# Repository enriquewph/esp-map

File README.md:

<!-- PROJECT SHIELDS -->
<div align="center">

[![Contributors][contributors-shield]][contributors-url]
[![Forks][forks-shield]][forks-url]
[![Stargazers][stars-shield]][stars-url]
[![Issues][issues-shield]][issues-url]
[![MIT License][license-shield]][license-url]

</div>

<p align="center">
  <picture>
    <source media="(prefers-color-scheme: dark)" srcset="docs/logo/espmap_nobg.svg">
    
  </picture>
</p>
<h1 align="center"><b>ESP</b> - <b>M</b>odular <b>A</b>utomation <b>P</b>latform</h1>
<h3 align="center">Modular hardware for IoT & home automation</h3>

<p align="center">
  <a href="https://github.com/enriquewph/esp-map"><strong>Explore the docs »</strong></a>
</p>

<!-- MARKDOWN LINKS & IMAGES -->
[contributors-shield]: https://img.shields.io/github/contributors/enriquewph/esp-map.svg?style=for-the-badge
[contributors-url]: https://github.com/enriquewph/esp-map/graphs/contributors
[forks-shield]: https://img.shields.io/github/forks/enriquewph/esp-map.svg?style=for-the-badge
[forks-url]: https://github.com/enriquewph/esp-map/network/members
[stars-shield]: https://img.shields.io/github/stars/enriquewph/esp-map.svg?style=for-the-badge
[stars-url]: https://github.com/enriquewph/esp-map/stargazers
[issues-shield]: https://img.shields.io/github/issues/enriquewph/esp-map.svg?style=for-the-badge
[issues-url]: https://github.com/enriquewph/esp-map/issues
[license-shield]: https://img.shields.io/github/license/enriquewph/esp-map.svg?style=for-the-badge
[license-url]: https://github.com/enriquewph/esp-map/blob/master/LICENSE.txt

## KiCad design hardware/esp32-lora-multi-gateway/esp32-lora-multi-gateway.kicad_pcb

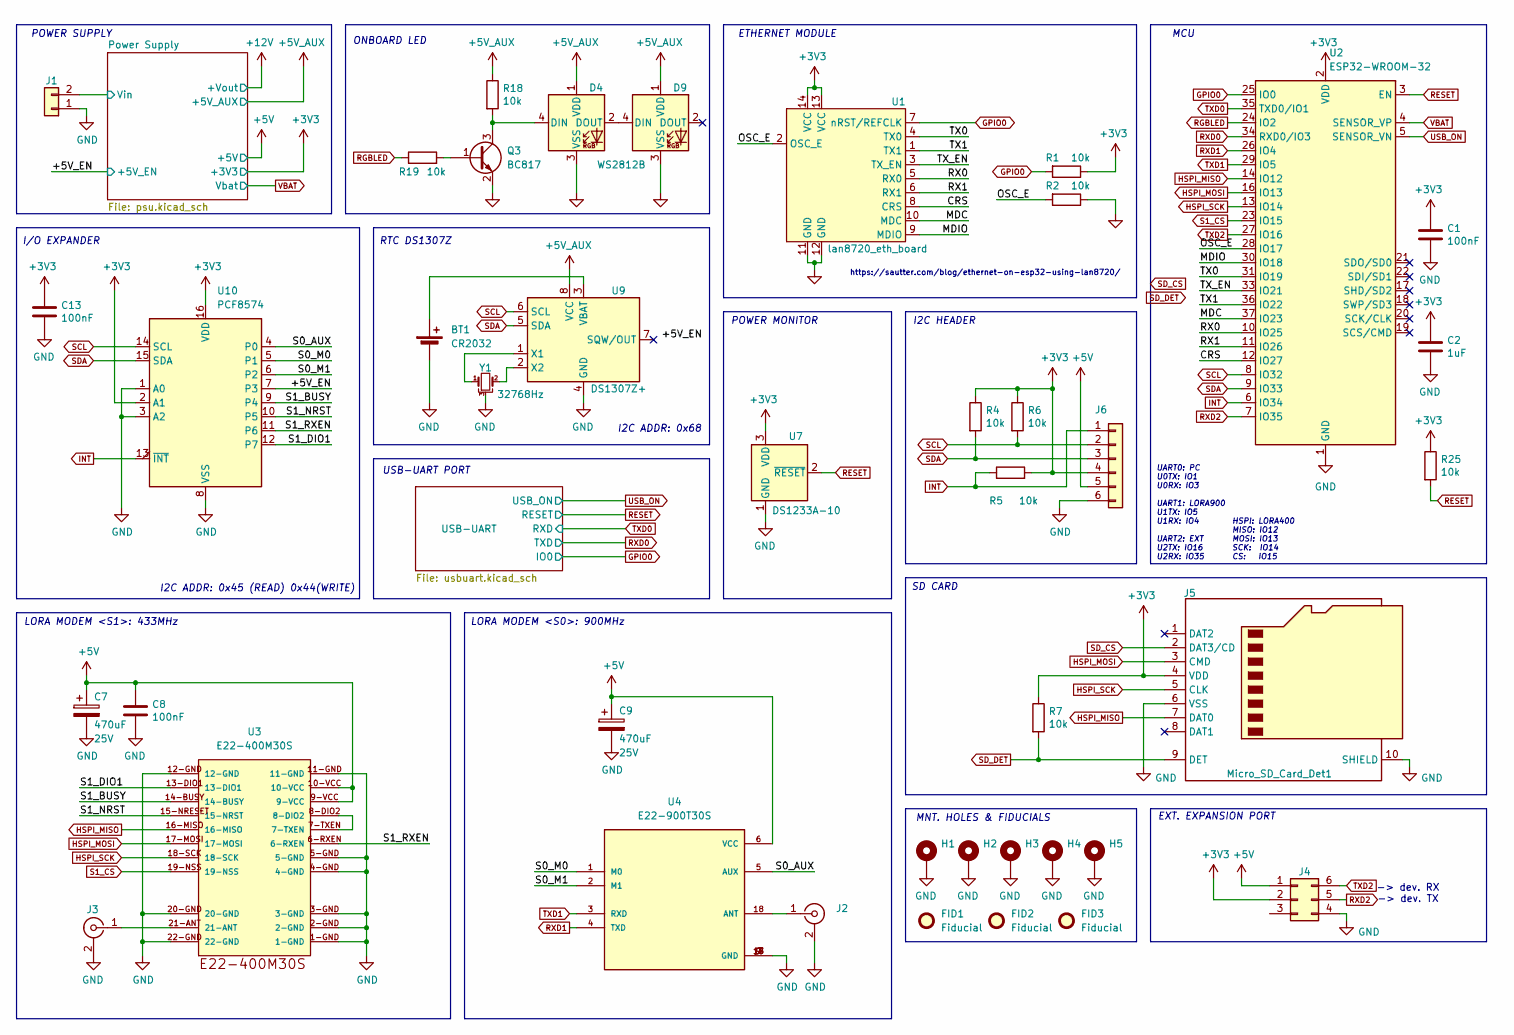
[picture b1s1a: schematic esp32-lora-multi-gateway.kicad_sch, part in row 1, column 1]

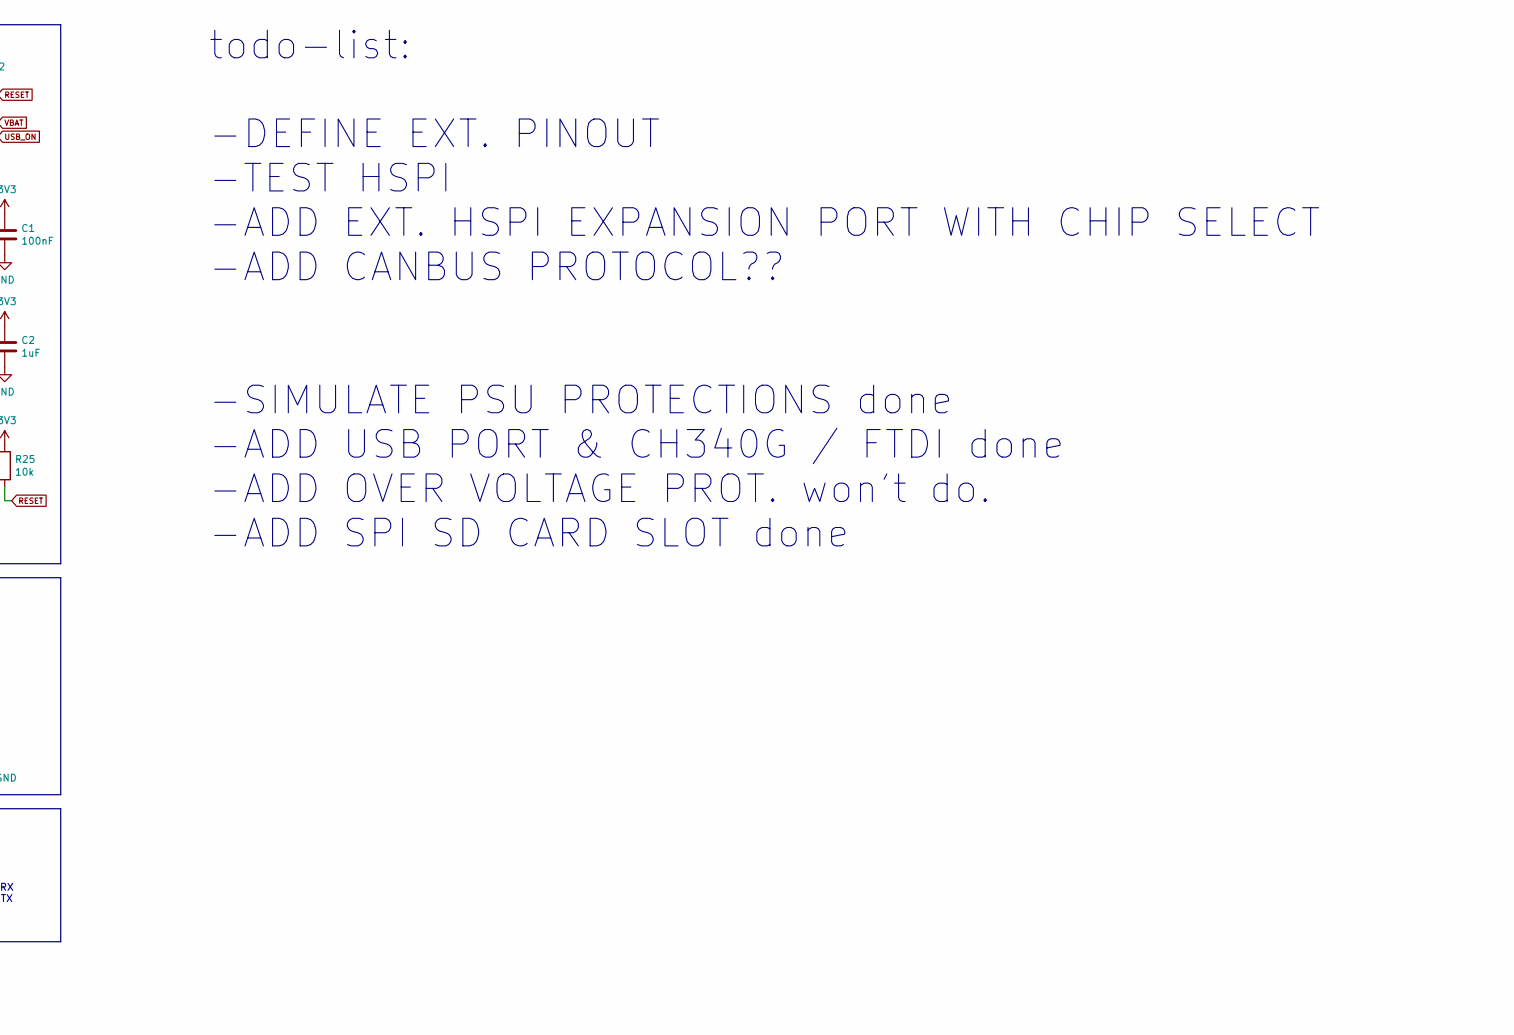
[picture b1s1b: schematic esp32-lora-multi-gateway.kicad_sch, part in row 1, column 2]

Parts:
BT1: CR2032; BatteryHolder_CR2032
C1, C8, C13: 100nF; C_1206_3216Metric_Pad1.33x1.80mm_HandSolder; Voltage 50V
C2: 1uF; C_1206_3216Metric_Pad1.33x1.80mm_HandSolder; Voltage 50V
C7, C9: 470uF; CAP_10x10_SMD_THT; Voltage 25V
D4, D9: WS2812B; LED_WS2812B_PLCC4_5.0x5.0mm_P3.2mm
FID1, FID2, FID3: Fiducial; Fiducial_0.5mm_Mask1mm
H1, H2, H3, H4, H5: MountingHole_Pad; MountingHole_3.5mm_Pad
J1: Conn_01x02; TerminalBlock-Bornier-2_P5.08mm
J2, J3: Conn_Coaxial; SMA_Molex_73251-2200_Horizontal
J4: Conn_02x03_Counter_Clockwise; PinHeader_2x03_P2.54mm_Vertical
J5: Micro_SD_Card_Det1; MicroSD_PUSH-PUSH
J6: Conn_01x06; Molex_KK-254_AE-6410-06A_1x06_P2.54mm_Vertical
Q3: BC817; SOT-23
R1, R2, R4, R5, R6, R7, R18, R19, R25: 10k; R_1206_3216Metric
U1: lan8720_eth_board; LAN8720-ETH-BOARD-90deg-CON-BOT
U2: ESP32-WROOM-32
U3: E22-400M30S
U4: E22-900T30S; PARTREV 1.4
U7: DS1233A-10; TO-92
U9: DS1307Z+; SOIC-8_3.9x4.9mm_P1.27mm
U10: PCF8574; SOIC-16W_7.5x10.3mm_P1.27mm
Y1: 32768Hz; Crystal_C38-LF_D3.0mm_L8.0mm_Horizontal_1EP_style1

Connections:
+3V3: C1.1, C2.1, C13.1, J4.2, J5.4 (VDD), J6.4, R1.1, R4.1, R5.2, R6.1, R7.1, R25.1, U1.13 (VCC), U1.14 (VCC), U2.2 (VDD), U7.3 (VDD), U10.2 (A1), U10.16 (VDD); also elsewhere on the board
+5V: C7.1, C8.1, C9.1, J4.1, J6.5, U3.9-VCC, U3.10-VCC, U4.6 (VCC); also elsewhere on the board
+5V_AUX: D4.1 (VDD), D9.1 (VDD), R18.1, U9.8 (VCC); also elsewhere on the board
/+5V_EN: U10.7 (P3); also elsewhere on the board
/CRS: U1.8 (CRS), U2.12 (IO27)
/MDC: U1.10 (MDC), U2.37 (IO23)
/MDIO: U1.9 (MDIO), U2.30 (IO18)
/OSC_E: R2.2, U1.2 (OSC_E), U2.28 (IO17)
/Power Supply/Vin: J1.2; also elsewhere on the board
/RX0: U1.5 (RX0), U2.10 (IO25)
/RX1: U1.6 (RX1), U2.11 (IO26)
/S0_AUX: U4.5 (AUX), U10.4 (P0)
/S0_M0: U4.1 (M0), U10.5 (P1)
/S0_M1: U4.2 (M1), U10.6 (P2)
/S1_BUSY: U3.14-BUSY, U10.9 (P4)
/S1_DIO1: U3.13-DIO1, U10.12 (P7)
/S1_NRST: U3.15-NRESET (15-NRST), U10.10 (P5)
/S1_RXEN: U3.6-RXEN, U10.11 (P6)
/TX0: U1.4 (TX0), U2.31 (IO19)
/TX1: U1.1 (TX1), U2.36 (IO22)
/TX_EN: U1.3 (TX_EN), U2.33 (IO21)
GND: BT1.2 (-), C1.2, C2.2, C7.2, C8.2, C9.2, C13.2, D4.3 (VSS), D9.3 (VSS), H1.1, H2.1, H3.1, H4.1, H5.1, J1.1, J2.2 (Ext), J3.2 (Ext), J4.4, J5.6 (VSS), J5.10 (SHIELD), J6.6, Q3.2 (E), R2.1, U1.11 (GND), U1.12 (GND), U2.1 (GND), U2.15 (GND), U2.38 (GND), U2.39 (GND), U3.1-GND, U3.2-GND, U3.3-GND, U3.4-GND, U3.5-GND, U3.11-GND, U3.12-GND, U3.20-GND, U3.22-GND, U4.7 (GND), U4.9 (GND), U4.15 (GND), U4.16 (GND), U4.17 (GND), U7.1 (GND), U9.4 (GND), U10.1 (A0), U10.3 (A2), U10.8 (VSS), Y1.3; also elsewhere on the board
GPIO0: R1.2, U1.7 (nRST/REFCLK), U2.25 (IO0); also elsewhere on the board
HSPI_MISO: J5.7 (DAT0), U2.14 (IO12), U3.16-MISO
HSPI_MOSI: J5.3 (CMD), U2.16 (IO13), U3.17-MOSI
HSPI_SCK: J5.5 (CLK), U2.13 (IO14), U3.18-SCK
INT: J6.1, R5.1, U2.6 (IO34), U10.13 (~INT)
unnamed: BT1.1 (+), U9.3 (VBAT)
unnamed: D4.4 (DIN), Q3.3 (C), R18.2
unnamed: D4.2 (DOUT), D9.4 (DIN)
unnamed: J2.1 (In), U4.18 (ANT)
unnamed: J3.1 (In), U3.21-ANT
unnamed: Q3.1 (B), R19.2
unnamed: U3.7-TXEN, U3.8-DIO2
unnamed: U9.1 (X1), Y1.1
unnamed: U9.2 (X2), Y1.2
RESET: R25.2, U2.3 (EN), U7.2 (~RESET); also elsewhere on the board
RGBLED: R19.1, U2.24 (IO2)
RXD0: U2.34 (RXD0/IO3); also elsewhere on the board
RXD1: U2.26 (IO4), U4.4 (TXD)
RXD2: J4.5, U2.7 (IO35)
S1_CS: U2.23 (IO15), U3.19-NSS
SCL: J6.2, R6.2, U2.8 (IO32), U9.6 (SCL), U10.14 (SCL)
SDA: J6.3, R4.2, U2.9 (IO33), U9.5 (SDA), U10.15 (SDA)
SD_CS: J5.2 (DAT3/CD)
SD_DET: J5.9 (DET), R7.2
TXD0: U2.35 (TXD0/IO1); also elsewhere on the board
TXD1: U2.29 (IO5), U4.3 (RXD)
TXD2: J4.6, U2.27 (IO16)
USB_ON: U2.5 (SENSOR_VN); also elsewhere on the board
VBAT: U2.4 (SENSOR_VP); also elsewhere on the board

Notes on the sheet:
HSPI: LORA400 MISO: IO12 MOSI: IO13 SCK: IO14 CS: IO15
RTC DS1307Z
https://sautter.com/blog/ethernet-on-esp32-using-lan8720/
POWER MONITOR
ETHERNET MODULE
POWER SUPPLY
LORA MODEM <S0>: 900MHz
MNT. HOLES & FIDUCIALS
SD CARD
-> dev. RX -> dev. TX
MCU
todo-list: -DEFINE EXT. PINOUT -TEST HSPI -ADD EXT. HSPI EXPANSION PORT WITH CHIP SELECT -ADD CANBUS PROTOCOL?? -SIMULATE PSU PROTECTIONS done -ADD USB PORT & CH340G / FTDI done -ADD OVER VOLTAGE PROT. won't do. -ADD SPI SD CARD SLOT done
UART0: PC U0TX: IO1 U0RX: IO3 UART1: LORA900 U1TX: IO5 U1RX: IO4 UART2: EXT U2TX: IO16 U2RX: IO35
LORA MODEM <S1>: 433MHz
I/O EXPANDER
I2C ADDR: 0x68
I2C HEADER
ONBOARD LED
EXT. EXPANSION PORT
USB-UART PORT
I2C ADDR: 0x45 (READ) 0x44(WRITE)

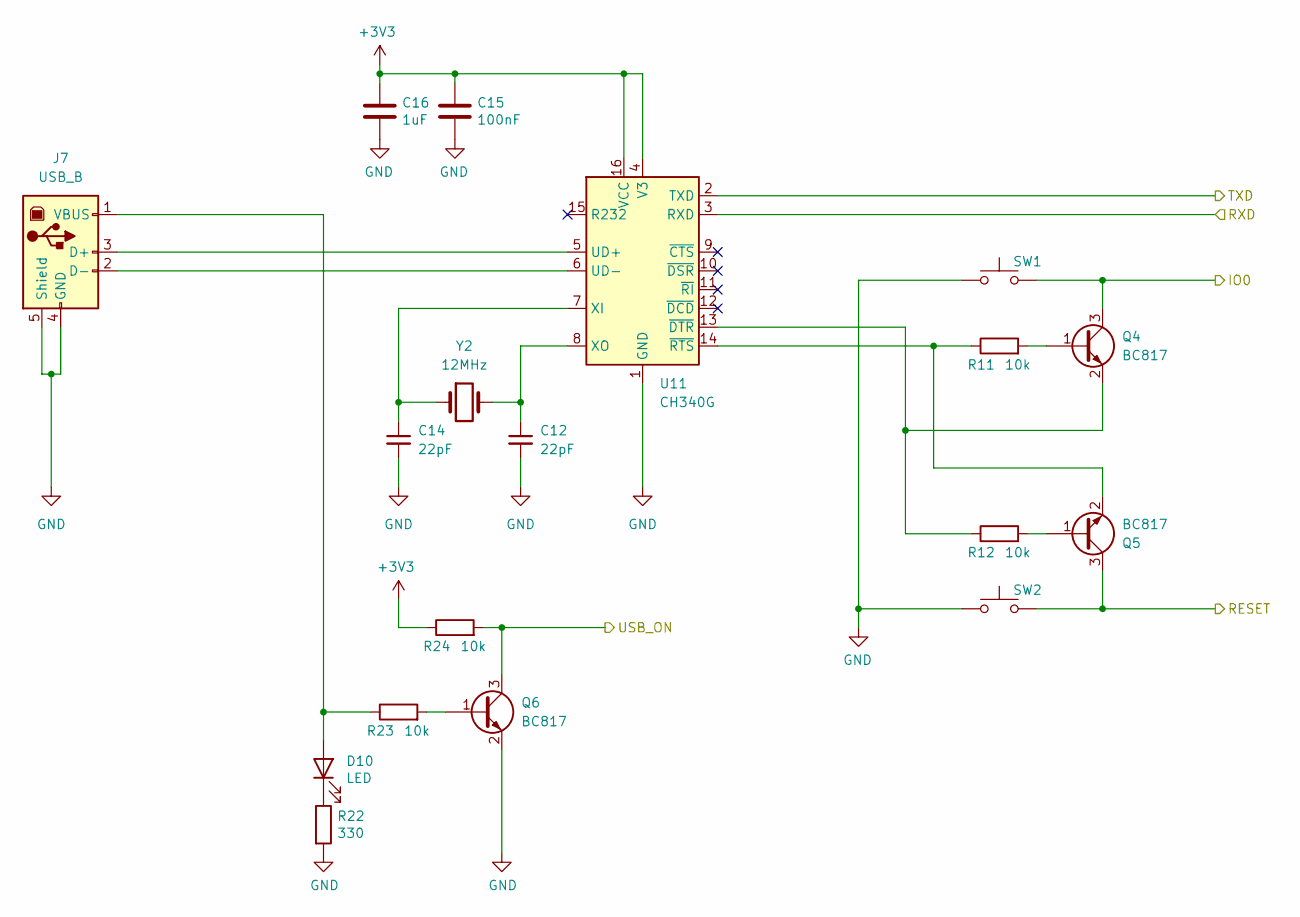
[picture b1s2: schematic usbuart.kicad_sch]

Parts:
C12, C14: 22pF; C_1206_3216Metric_Pad1.33x1.80mm_HandSolder
C15: 100nF; C_1206_3216Metric_Pad1.33x1.80mm_HandSolder; Voltage 50V
C16: 1uF; C_1206_3216Metric_Pad1.33x1.80mm_HandSolder; Voltage 50V
D10: LED; LED_1206_3216Metric
J7: USB_B; USB_B_OST_USB-B1HSxx_Horizontal
Q4, Q5, Q6: BC817; SOT-23
R11, R12, R23, R24: 10k; R_1206_3216Metric
R22: 330; R_1206_3216Metric
SW1, SW2: SW_Push; SW_PUSH_6mm
U11: CH340G; SOIC-16_3.9x9.9mm_P1.27mm
Y2: 12MHz; Crystal_HC49-U_Vertical

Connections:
+3V3: C15.1, C16.1, R24.1, U11.4 (V3), U11.16 (VCC); also elsewhere on the board
GND: C12.2, C14.2, C15.2, C16.2, J7.4 (GND), J7.5 (Shield), Q6.2 (E), R22.2, SW1.1, SW2.1, U11.1 (GND); also elsewhere on the board
GPIO0: Q4.3 (C), SW1.2; also elsewhere on the board
unnamed: D10.2 (A), J7.1 (VBUS), R23.1
unnamed: D10.1 (K), R22.1
unnamed: J7.3 (D+), U11.5 (UD+)
unnamed: J7.2 (D-), U11.6 (UD-)
unnamed: Q4.1 (B), R11.2
unnamed: Q4.2 (E), R12.1, U11.13 (~DTR)
unnamed: Q5.1 (B), R12.2
unnamed: Q5.2 (E), R11.1, U11.14 (~RTS)
unnamed: Q6.1 (B), R23.2
unnamed: C14.1, U11.7 (XI), Y2.1
unnamed: C12.1, U11.8 (XO), Y2.2
RESET: Q5.3 (C), SW2.2; also elsewhere on the board
RXD0: U11.2 (TXD); also elsewhere on the board
TXD0: U11.3 (RXD); also elsewhere on the board
USB_ON: Q6.3 (C), R24.2; also elsewhere on the board

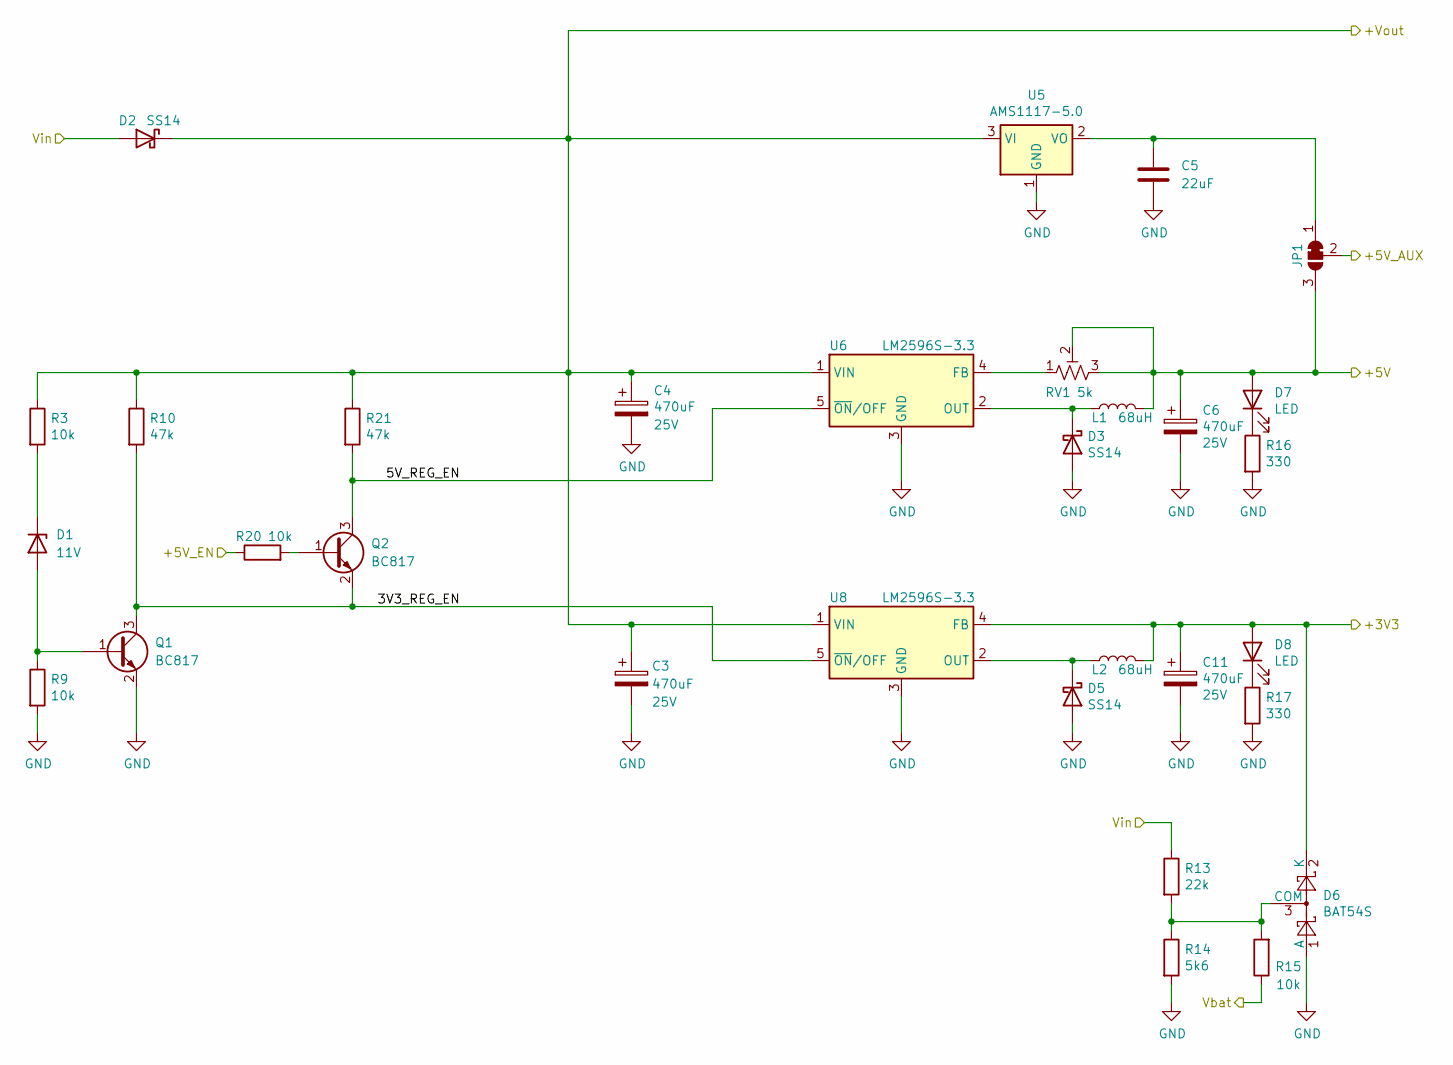
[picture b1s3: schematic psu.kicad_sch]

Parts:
C3, C4, C6, C11: 470uF; CAP_10x10_SMD_THT; Voltage 25V
C5: 22uF; C_1812_4532Metric_Pad1.57x3.40mm_HandSolder
D1: 11V; D_DO-15_P3.81mm_Vertical_AnodeUp
D2, D3, D5: SS14; D_SMA_Handsoldering
D6: BAT54S; SOT-23
D7, D8: LED; LED_1206_3216Metric
JP1: SolderJumper_3_Bridged12; SolderJumper-3_P1.3mm_Bridged12_RoundedPad1.0x1.5mm
L1, L2: 68uH; L_12x12mm_H8mm
Q1, Q2: BC817; SOT-23
R3, R9, R15, R20: 10k; R_1206_3216Metric
R10, R21: 47k; R_1206_3216Metric
R13: 22k; R_Axial_DIN0207_L6.3mm_D2.5mm_P2.54mm_Vertical
R14: 5k6; R_Axial_DIN0207_L6.3mm_D2.5mm_P2.54mm_Vertical
R16, R17: 330; R_1206_3216Metric
RV1: 5k; Potentiometer_Bourns_3296W_Vertical
U5: AMS1117-5.0; SOT-223-3_TabPin2
U6, U8: LM2596S-3.3; TO-263-5_TabPin3

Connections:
+3V3: C11.1, D6.2 (K), D8.2 (A), L2.2, U8.4 (FB); also elsewhere on the board
+5V: C6.1, D7.2 (A), JP1.3 (B), L1.2, RV1.2, RV1.3; also elsewhere on the board
+5V_AUX: JP1.2 (C); also elsewhere on the board
+12V: C3.1, C4.1, D2.1 (K), R3.1, R10.1, R21.1, U5.3 (VI), U6.1 (VIN), U8.1 (VIN)
/+5V_EN: R20.1; also elsewhere on the board
/Power Supply/3V3_REG_EN: Q1.3 (C), Q2.2 (E), R10.2, U8.5 (~ON/OFF)
/Power Supply/5V_REG_EN: Q2.3 (C), R21.2, U6.5 (~ON/OFF)
/Power Supply/Vin: D2.2 (A), R13.1; also elsewhere on the board
GND: C3.2, C4.2, C5.2, C6.2, C11.2, D3.2 (A), D5.2 (A), D6.1 (A), Q1.2 (E), R9.2, R14.2, R16.2, R17.2, U5.1 (GND), U6.3 (GND), U8.3 (GND); also elsewhere on the board
unnamed: D1.2 (A), Q1.1 (B), R9.1
unnamed: D1.1 (K), R3.2
unnamed: D3.1 (K), L1.1, U6.2 (OUT)
unnamed: D5.1 (K), L2.1, U8.2 (OUT)
unnamed: D6.3 (COM), R13.2, R14.1, R15.2
unnamed: D7.1 (K), R16.1
unnamed: D8.1 (K), R17.1
unnamed: C5.1, JP1.1 (A), U5.2 (VO)
unnamed: Q2.1 (B), R20.2
unnamed: RV1.1, U6.4 (FB)
VBAT: R15.1; also elsewhere on the board

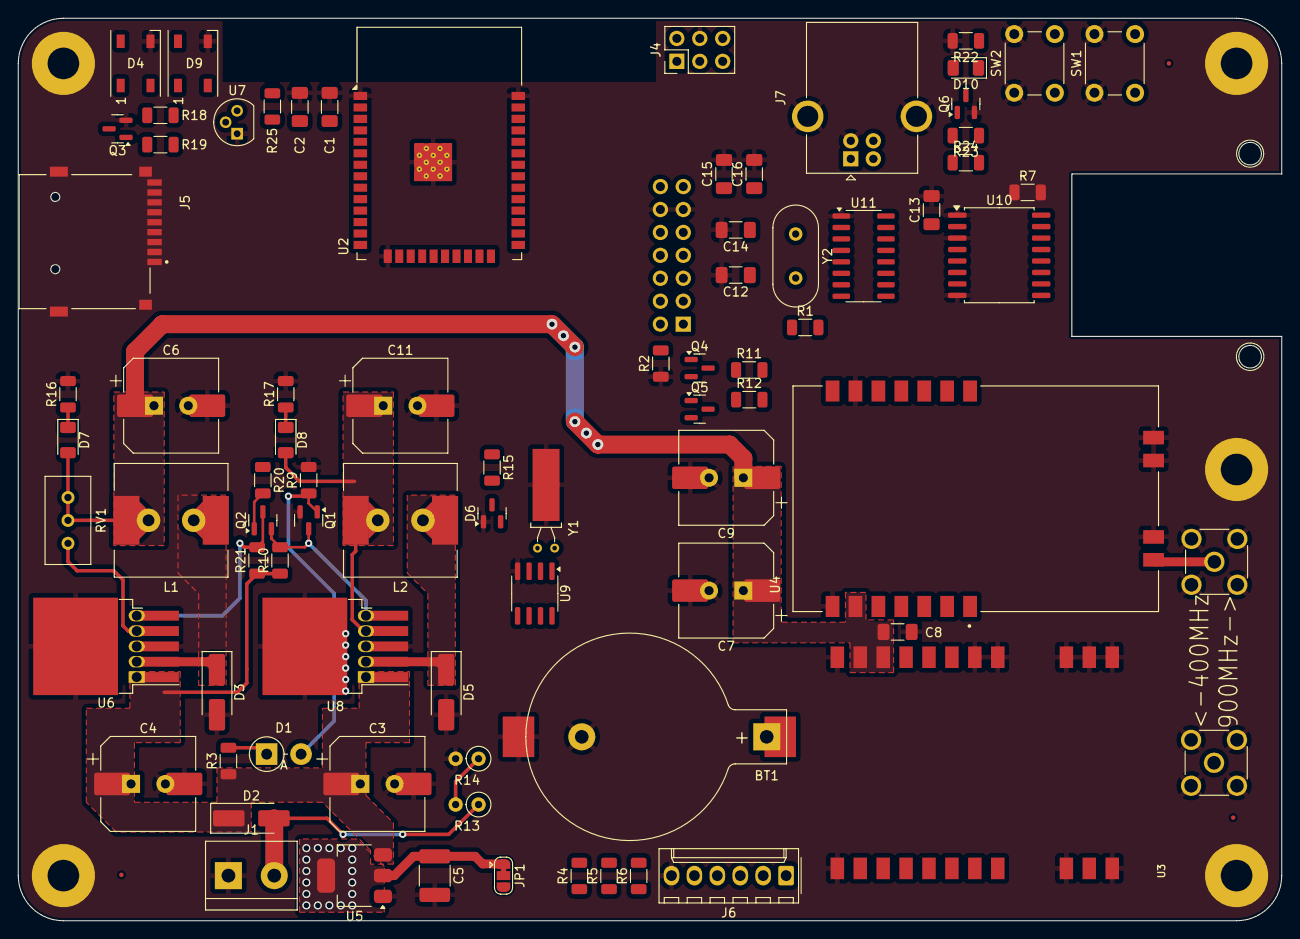
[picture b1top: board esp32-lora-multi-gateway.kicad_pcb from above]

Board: 2 copper layers, 140.0 x 100.0 mm, 90 parts (0 on the bottom side), 74 nets.

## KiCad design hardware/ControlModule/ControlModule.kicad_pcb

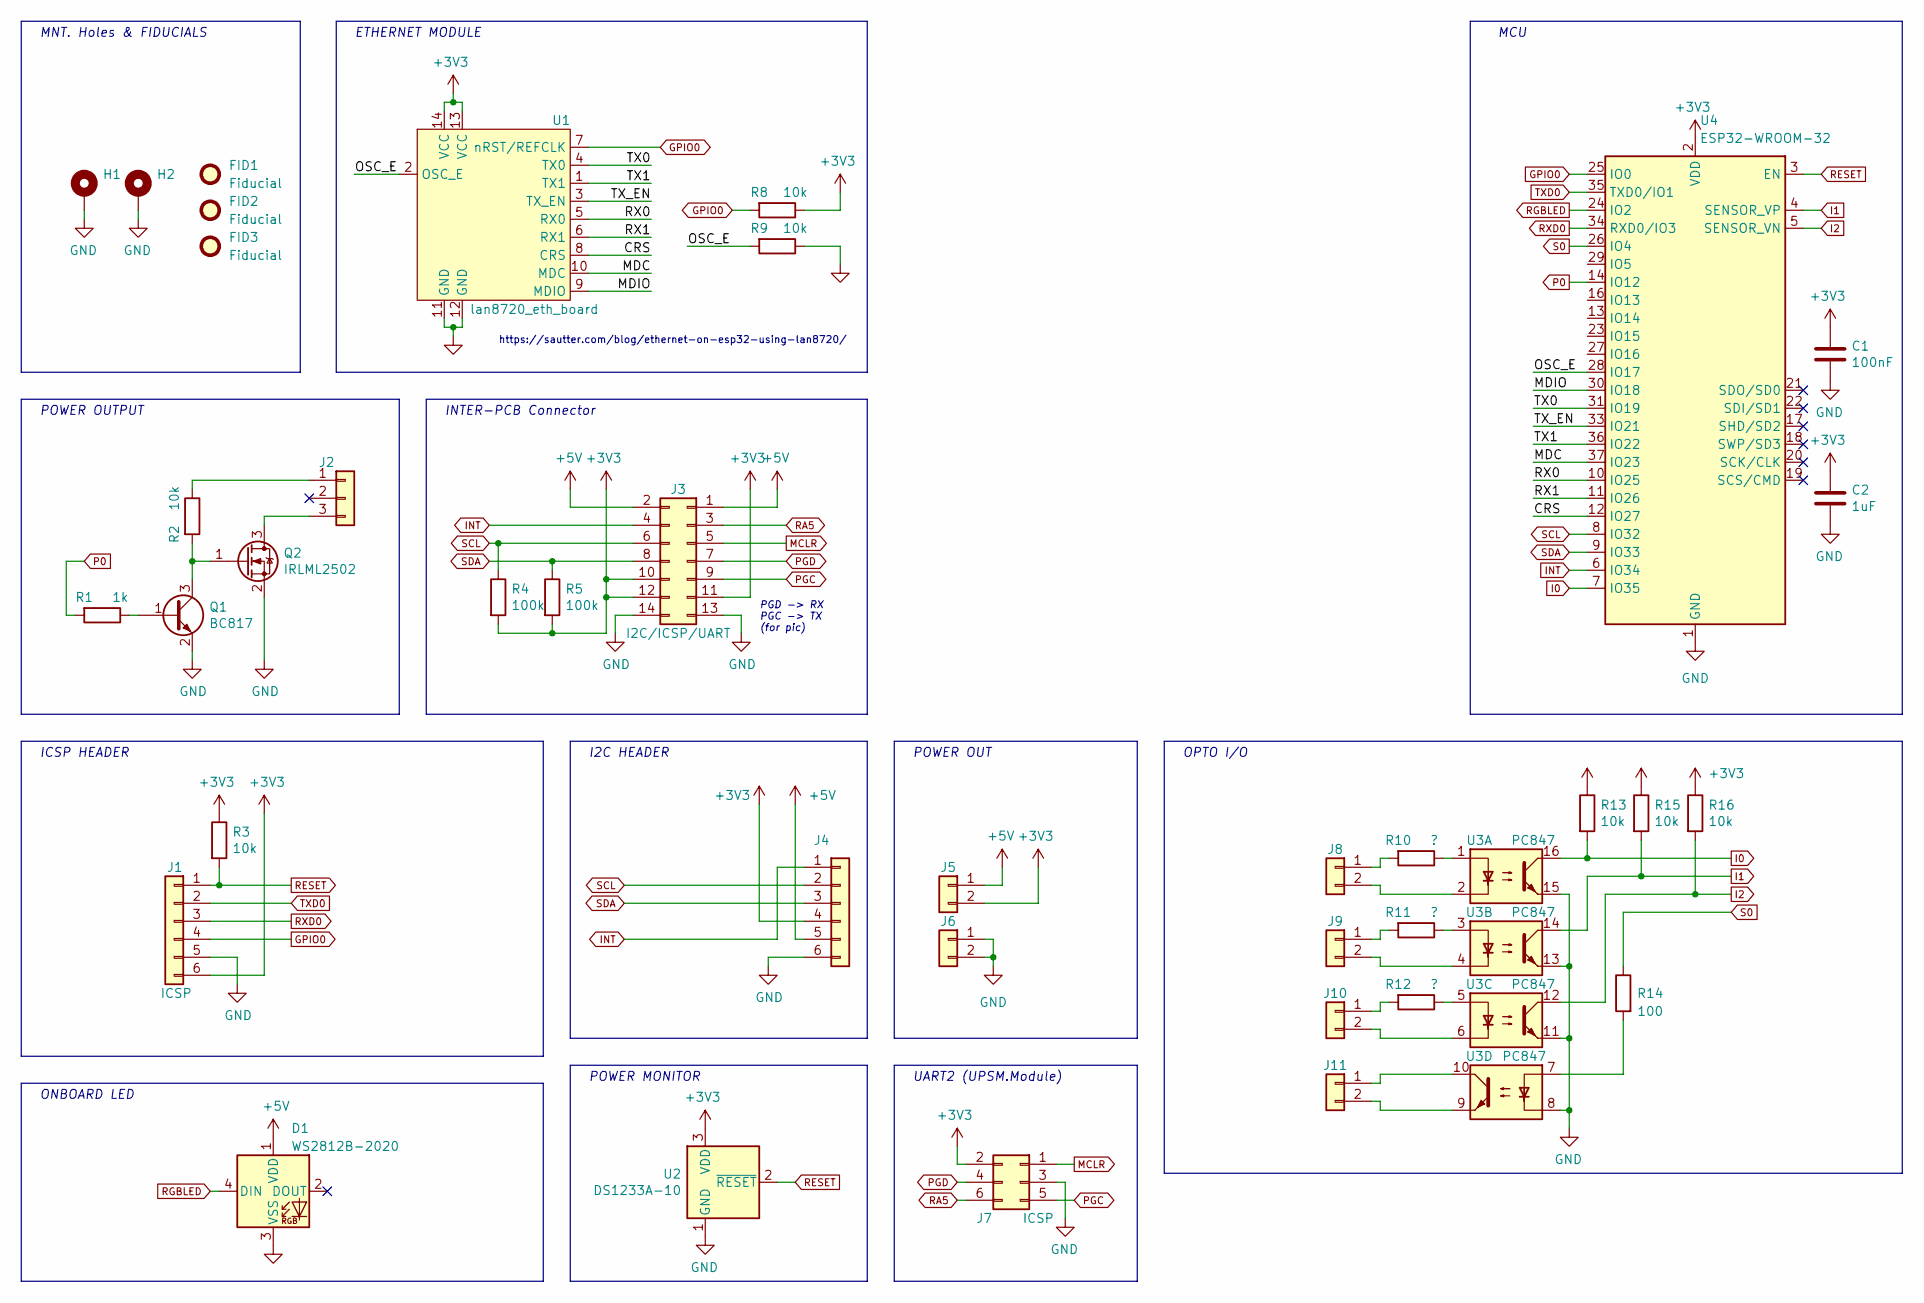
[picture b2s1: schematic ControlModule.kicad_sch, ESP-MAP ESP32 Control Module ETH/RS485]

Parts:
C1: 100nF; C_1206_3216Metric_Pad1.33x1.80mm_HandSolder; Voltage 50V
C2: 1uF; C_1206_3216Metric_Pad1.33x1.80mm_HandSolder; Voltage 50V
D1: WS2812B-2020; LED_WS2812-2020
FID1, FID2, FID3: Fiducial; Fiducial_0.5mm_Mask1mm
H1, H2: MountingHole_Pad; MountingHole_3.5mm_Pad
J1: ICSP; PinSocket_1x06_P2.54mm_Vertical
J2: Conn_01x03; Molex_KK-254_AE-6410-03A_1x03_P2.54mm_Vertical
J3: I2C/ICSP/UART; PinSocket_2x07_P2.54mm_Vertical
J4: Conn_01x06; Molex_KK-254_AE-6410-06A_1x06_P2.54mm_Vertical
J5, J6, J8, J9, J10, J11: Conn_01x02; TerminalBlock-Bornier-2_P5.08mm
J7: ICSP; PinHeader_2x03_P2.54mm_Vertical
Q1: BC817; SOT-23
Q2: IRLML2502; SOT-23
R1: 1k; R_1206_3216Metric
R2, R3, R8, R9, R13, R15, R16: 10k; R_1206_3216Metric
R4, R5: 100k; R_1206_3216Metric
R10, R11, R12: ?; R_Axial_DIN0207_L6.3mm_D2.5mm_P2.54mm_Vertical
R14: 100; R_1206_3216Metric
U1: lan8720_eth_board; LAN8720-ETH-BOARD-90deg-CON-BOT
U2: DS1233A-10; TO-92
U3: PC847; SMDIP-16_W9.53mm
U4: ESP32-WROOM-32

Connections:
+3V3: C1.1, C2.1, J1.6, J3.10, J3.11, J3.12, J4.4, J5.2, J7.2, R3.1, R4.2, R5.2, R8.1, R13.1, R15.1, R16.1, U1.13 (VCC), U1.14 (VCC), U2.3 (VDD), U4.2 (VDD)
+5V: D1.1 (VDD), J3.1, J3.2, J4.5, J5.1
/CRS: U1.8 (CRS), U4.12 (IO27)
/MDC: U1.10 (MDC), U4.37 (IO23)
/MDIO: U1.9 (MDIO), U4.30 (IO18)
/OSC_E: R9.2, U1.2 (OSC_E), U4.28 (IO17)
/RX0: U1.5 (RX0), U4.10 (IO25)
/RX1: U1.6 (RX1), U4.11 (IO26)
/TX0: U1.4 (TX0), U4.31 (IO19)
/TX1: U1.1 (TX1), U4.36 (IO22)
/TX_EN: U1.3 (TX_EN), U4.33 (IO21)
GND: C1.2, C2.2, D1.3 (VSS), H1.1, H2.1, J1.5, J3.13, J3.14, J4.6, J6.1, J6.2, J7.3, Q1.2 (E), Q2.2 (S), R9.1, U1.11 (GND), U1.12 (GND), U2.1 (GND), U3.8, U3.11, U3.13, U3.15, U4.1 (GND), U4.15 (GND), U4.38 (GND), U4.39 (GND)
GPIO0: J1.4, R8.2, U1.7 (nRST/REFCLK), U4.25 (IO0)
I0: R13.2, U3.16, U4.7 (IO35)
I1: R15.2, U3.14, U4.4 (SENSOR_VP)
I2: R16.2, U3.12, U4.5 (SENSOR_VN)
INT: J3.4, J4.1, U4.6 (IO34)
MCLR: J3.5, J7.1
unnamed: J2.1, R2.1
unnamed: J2.3, Q2.3 (D)
unnamed: J8.1, R10.2
unnamed: J8.2, U3.2
unnamed: J9.1, R11.2
unnamed: J9.2, U3.4
unnamed: J10.1, R12.2
unnamed: J10.2, U3.6
unnamed: J11.1, U3.10
unnamed: J11.2, U3.9
unnamed: Q1.1 (B), R1.1
unnamed: Q1.3 (C), Q2.1 (G), R2.2
unnamed: R10.1, U3.1
unnamed: R11.1, U3.3
unnamed: R12.1, U3.5
unnamed: R14.2, U3.7
P0: R1.2, U4.14 (IO12)
PGC: J3.9, J7.5
PGD: J3.7, J7.4
RA5: J3.3, J7.6
RESET: J1.1, R3.2, U2.2 (~RESET), U4.3 (EN)
RGBLED: D1.4 (DIN), U4.24 (IO2)
RXD0: J1.3, U4.34 (RXD0/IO3)
S0: R14.1, U4.26 (IO4)
SCL: J3.6, J4.2, R4.1, U4.8 (IO32)
SDA: J3.8, J4.3, R5.1, U4.9 (IO33)
TXD0: J1.2, U4.35 (TXD0/IO1)

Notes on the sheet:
POWER OUT
ICSP HEADER
INTER-PCB Connector
OPTO I/O
MCU
https://sautter.com/blog/ethernet-on-esp32-using-lan8720/
POWER OUTPUT
MNT. Holes & FIDUCIALS
UART2 (UPSM.Module)
PGD -> RX PGC -> TX (for pic)
POWER MONITOR
I2C HEADER
ONBOARD LED
ETHERNET MODULE

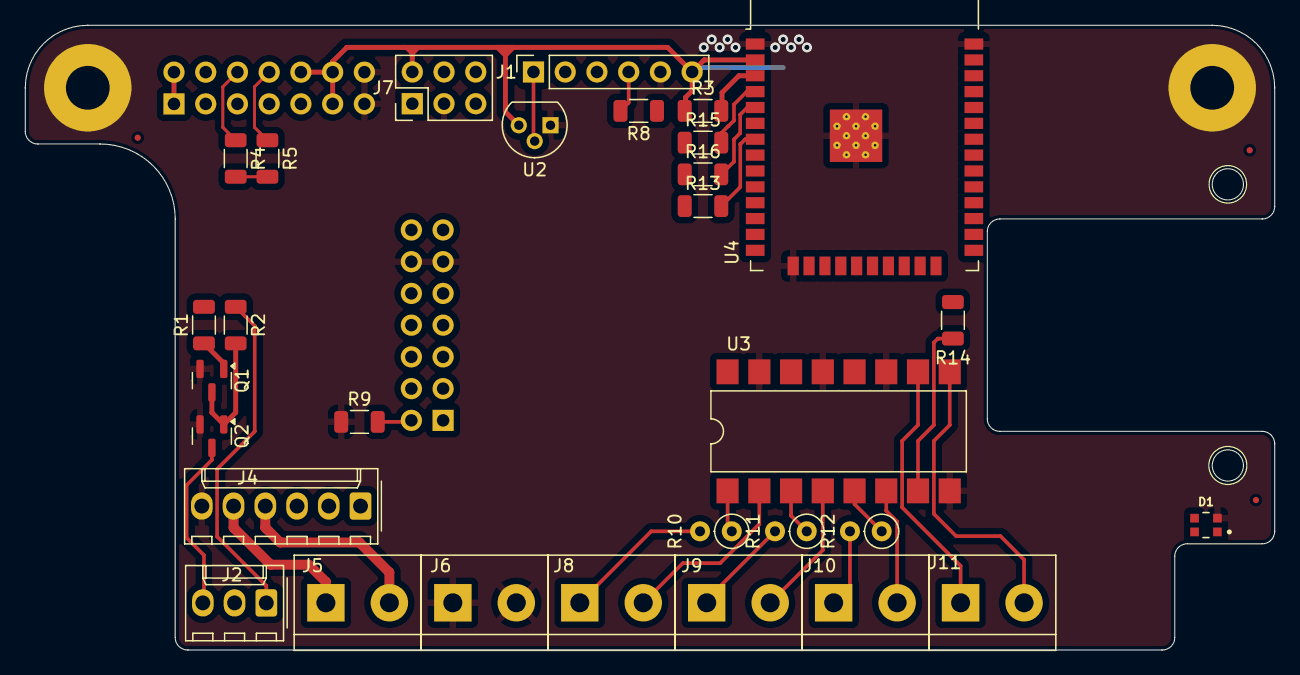
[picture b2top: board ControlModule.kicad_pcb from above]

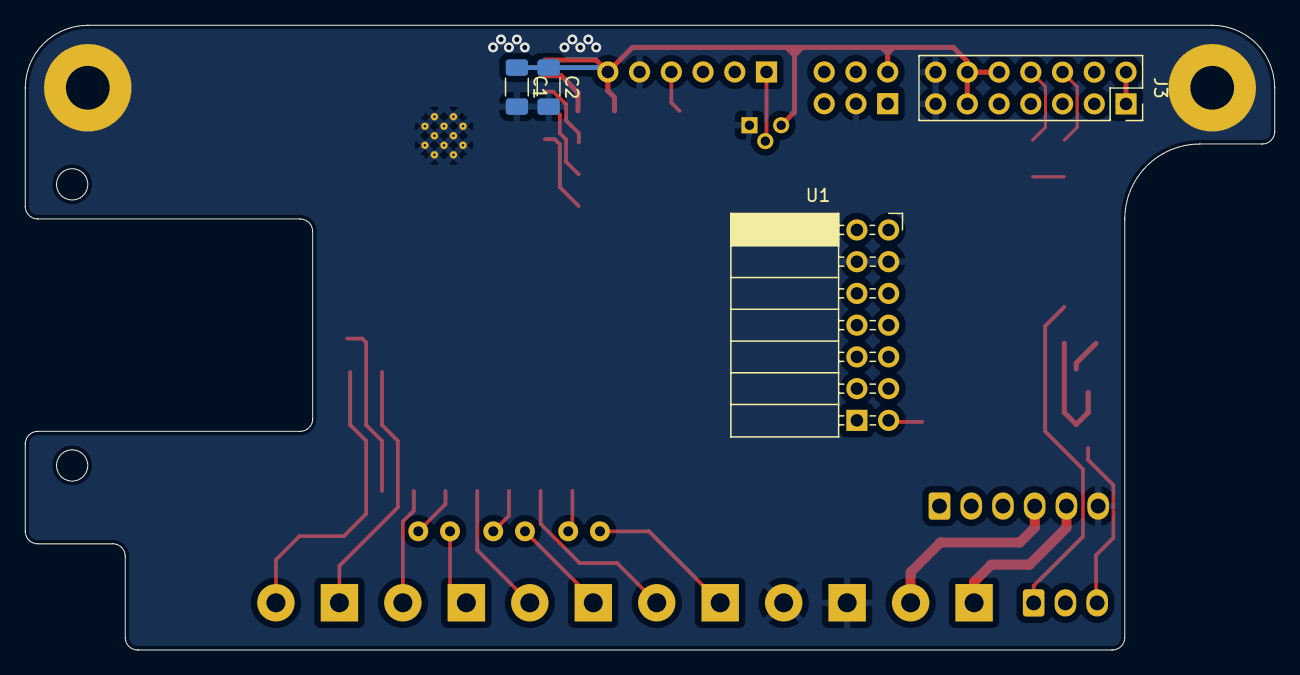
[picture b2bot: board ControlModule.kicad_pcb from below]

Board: 2 copper layers, 100.0 x 50.0 mm, 39 parts (3 on the bottom side), 45 nets.
